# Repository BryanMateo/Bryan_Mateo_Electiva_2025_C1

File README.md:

# Bryan_Mateo_Electiva_2025_C1
Repositorio de la asignatura Electiva Mecatrónica 2025-C1.

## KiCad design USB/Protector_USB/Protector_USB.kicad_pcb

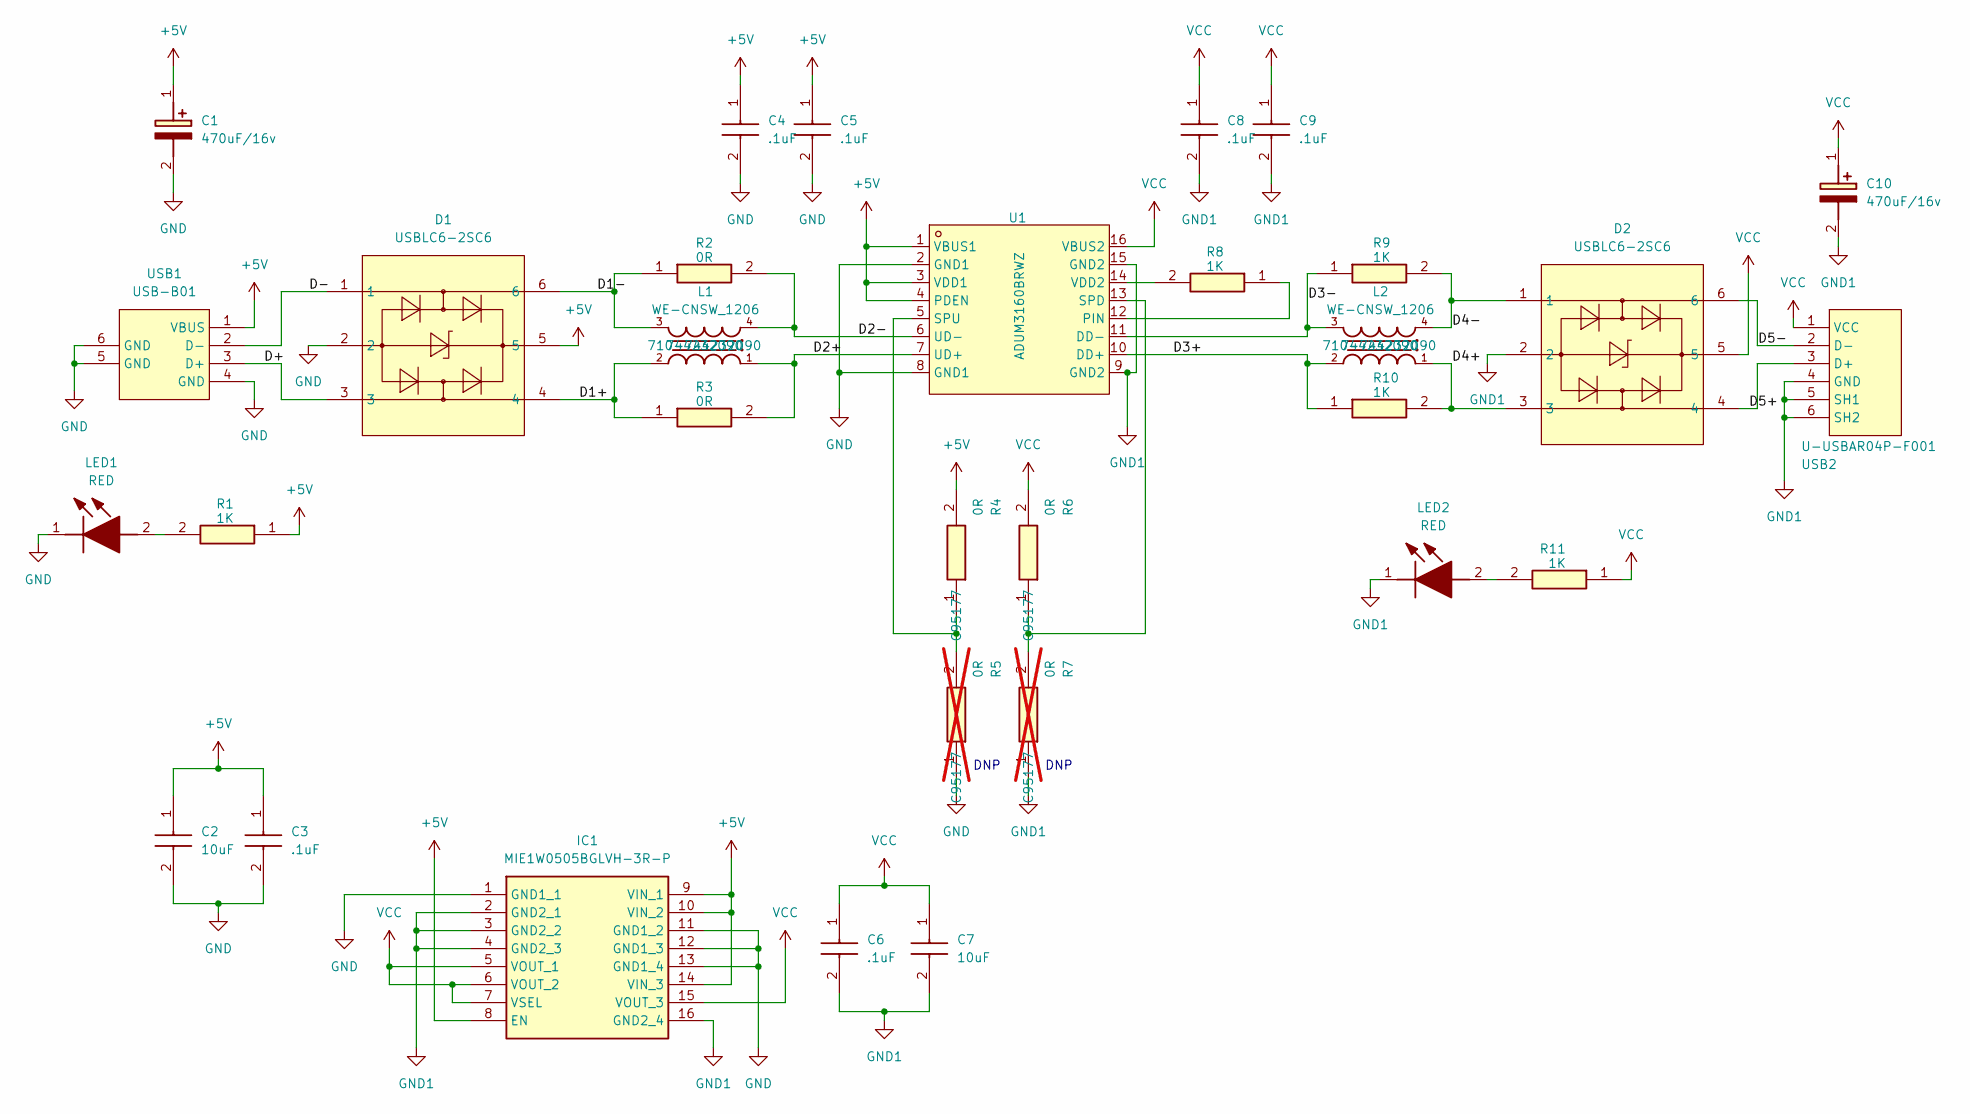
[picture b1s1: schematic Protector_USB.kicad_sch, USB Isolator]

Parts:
C1, C10: 470uF/16v; EEE1AA220WR; Mouser Part Number 667-EEE-FN1C470UR
C2, C7: 10uF; CAPC1608X102N; Mouser Part Number 581-0603YD106KAT2A
C3, C4, C5, C6, C8, C9: .1uF; CAPC1608X90N; Mouser Part Number 581-0603YC104J4T2A
D1, D2: USBLC6-2SC6; SOT-23-6_L2.9-W1.6-P0.95-LS2.8-BL; LCSC Part C7519
IC1: MIE1W0505BGLVH-3R-P; MIE1W0505BGLVH3RP; Mouser Part Number 946-MIE1W0505BGLVH3P
L1, L2: WE-CNSW_1206; WE-CNSW_1206_WE-CNSW_1206; Manufacturer_Part_Number 744232090; Mouser Part Number 710-744232090
LED1, LED2: RED; KSEELP4122P1R258A8J8020R18; Mouser Part Number 720-P412P1R258A8J802
R1, R8, R9, R10, R11: 1K; RESC1608X55N; Mouser Part Number 603-RT0603FRE071KL
R2, R3: 0R; RESC1608X55N; Mouser Part Number 603-RC0603FR-070RL; LCSC Part C95177
R4, R6: 0R; RESC1608X55N; Mouser Part Number 603-RC0603FR-070RL
R5, R7: 0R; RESC1608X55N; Mouser Part Number 603-RC0603FR-070RL; not fitted
U1: ADUM3160BRWZ; WSOIC-16_L10.3-W7.5-P1.27-LS10.3-BL; LCSC Part C108501
USB1: USB-B01; USB-B-TH_USB-B01; LCSC Part C498173
USB2: U-USBAR04P-F001; USB-A-TH_USB-302-T; LCSC Part C386736

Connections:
+5V: C1.1 (+), C2.1, C3.1, C4.1, C5.1, D1.5, IC1.8 (EN), IC1.9 (VIN_1), IC1.10 (VIN_2), IC1.14 (VIN_3), R1.1, R4.2, U1.1 (VBUS1), U1.3 (VDD1), U1.4 (PDEN), USB1.1 (VBUS)
/D1+: D1.4, L1.2, R3.1
/D1-: D1.6, L1.3, R2.1
/D2+: L1.1, R3.2, U1.7 (UD+)
/D2-: L1.4, R2.2, U1.6 (UD-)
/D3+: L2.2, R10.1, U1.10 (DD+)
/D3-: L2.3, R9.1, U1.11 (DD-)
/D4+: D2.3, L2.1, R10.2
/D4-: D2.1, L2.4, R9.2
/D5+: D2.4, USB2.3 (D+)
/D5-: D2.6, USB2.2 (D-)
/D+: D1.3, USB1.3 (D+)
/D-: D1.1, USB1.2 (D-)
GND: C1.2 (-), C2.2, C3.2, C4.2, C5.2, D1.2, IC1.1 (GND1_1), IC1.11 (GND1_2), IC1.12 (GND1_3), IC1.13 (GND1_4), LED1.1 (K), R5.1, U1.2 (GND1), U1.8 (GND1), USB1.4 (GND), USB1.5 (GND), USB1.6 (GND)
GND1: C6.2, C7.2, C8.2, C9.2, C10.2 (-), D2.2, IC1.2 (GND2_1), IC1.3 (GND2_2), IC1.4 (GND2_3), IC1.16 (GND2_4), LED2.1 (K), R7.1, U1.9 (GND2), U1.15 (GND2), USB2.4 (GND), USB2.5 (SH1), USB2.6 (SH2)
unnamed: LED1.2 (A), R1.2
unnamed: LED2.2 (A), R11.2
unnamed: R8.1, U1.12 (PIN)
unnamed: R6.1, R7.2, U1.13 (SPD)
unnamed: R4.1, R5.2, U1.5 (SPU)
unnamed: R8.2, U1.14 (VDD2)
VCC: C6.1, C7.1, C8.1, C9.1, C10.1 (+), D2.5, IC1.5 (VOUT_1), IC1.6 (VOUT_2), IC1.7 (VSEL), IC1.15 (VOUT_3), R6.2, R11.1, U1.16 (VBUS2), USB2.1 (VCC)

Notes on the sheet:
DNP

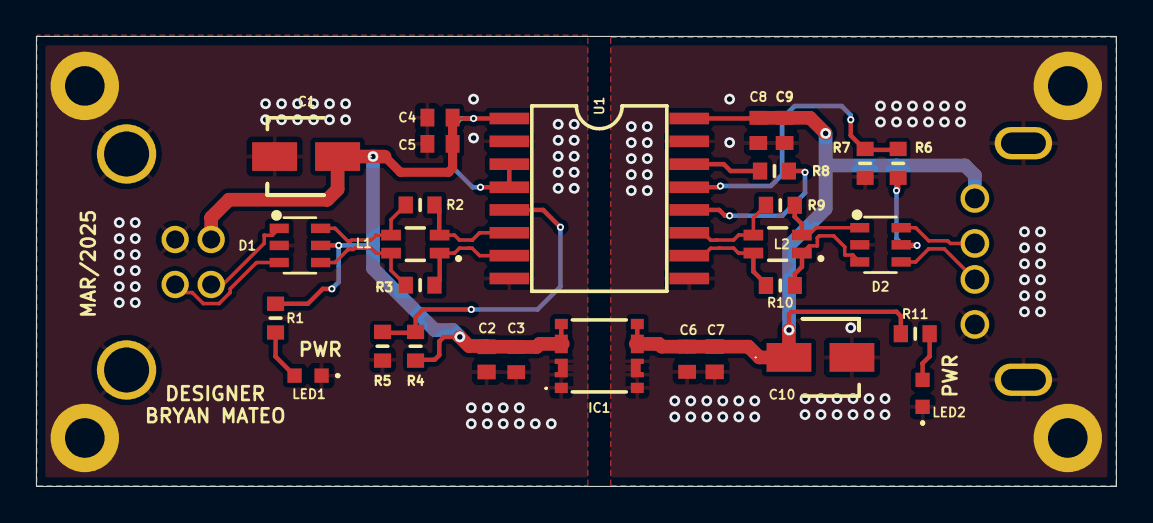
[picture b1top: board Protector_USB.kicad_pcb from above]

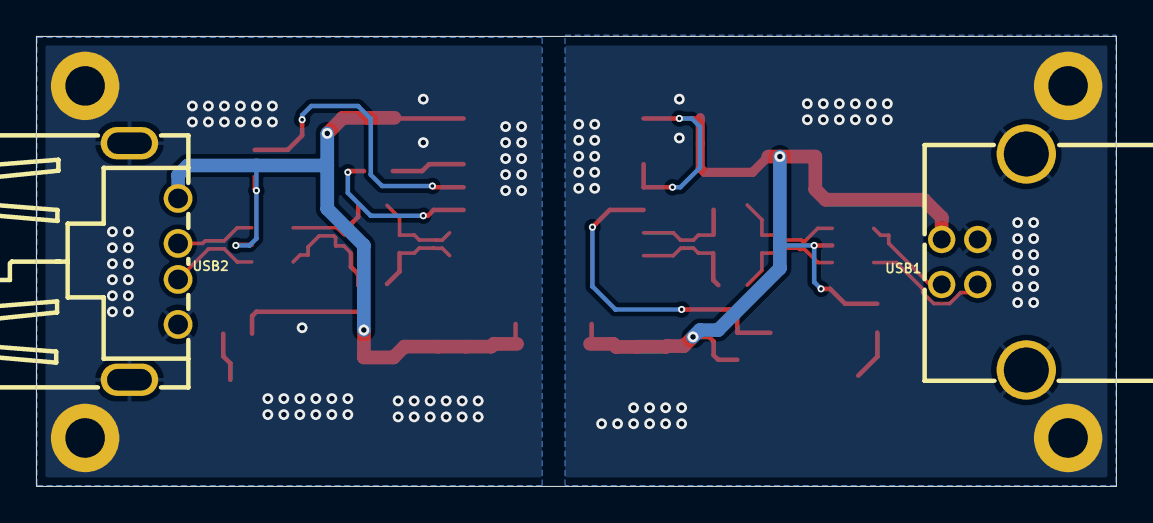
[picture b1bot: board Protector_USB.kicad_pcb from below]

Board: 2 copper layers, 60.0 x 25.0 mm, 31 parts (2 on the bottom side), 22 nets.

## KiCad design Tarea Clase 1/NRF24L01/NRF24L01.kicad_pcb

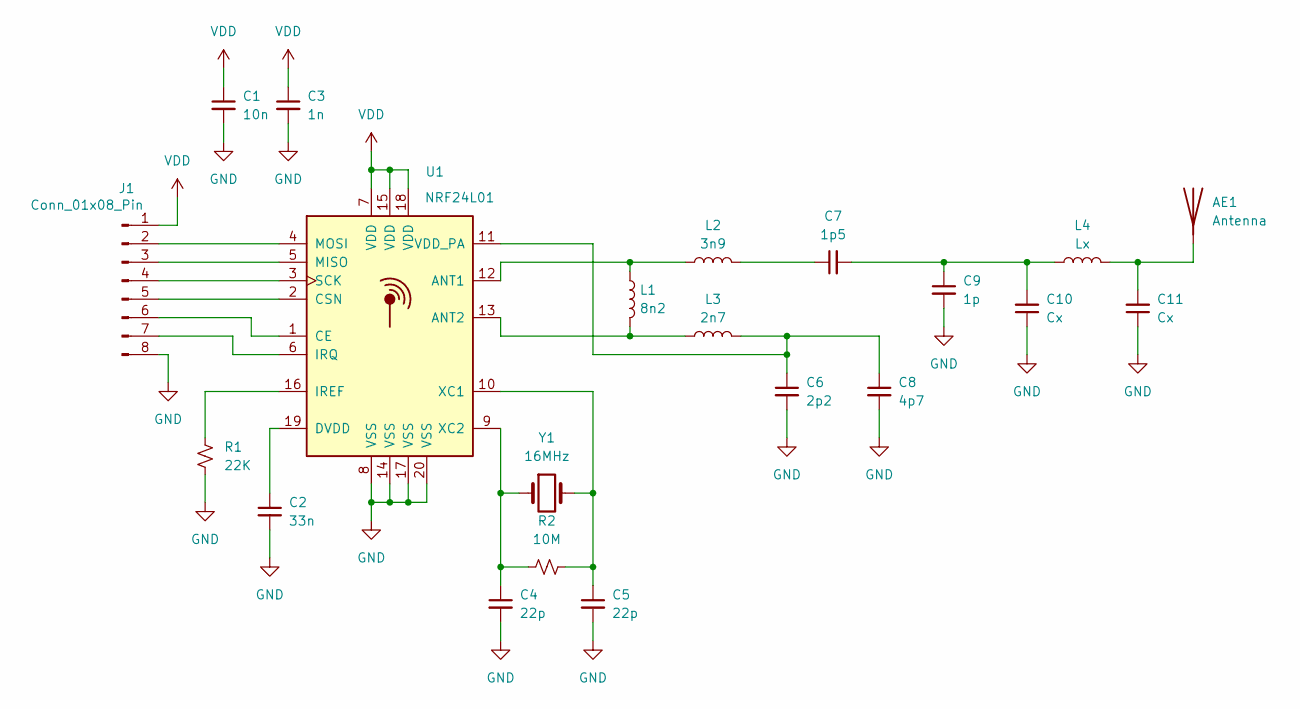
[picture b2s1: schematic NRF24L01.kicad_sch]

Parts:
AE1: Antenna; Texas_SWRA117D_2.4GHz_Right
C1: 10n; C_0402_1005Metric
C2: 33n; C_0402_1005Metric
C3: 1n; C_0402_1005Metric
C4, C5: 22p; C_0402_1005Metric
C6: 2p2; C_0402_1005Metric
C7: 1p5; C_0402_1005Metric
C8: 4p7; C_0402_1005Metric
C9: 1p; C_0402_1005Metric
C10, C11: Cx; C_0402_1005Metric
J1: Conn_01x08_Pin; Hirose_DF13-08P-1.25DSA_1x08_P1.25mm_Vertical
L1: 8n2; L_0402_1005Metric
L2: 3n9; L_0402_1005Metric
L3: 2n7; L_0402_1005Metric
L4: Lx; L_0402_1005Metric
R1: 22K; C_0402_1005Metric
R2: 10M; C_0402_1005Metric
U1: NRF24L01; QFN-20-1EP_4x4mm_P0.5mm_EP2.5x2.5mm
Y1: 16MHz; Crystal_SMD_3215-2Pin_3.2x1.5mm

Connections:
GND: AE1.2, C1.2, C2.2, C3.2, C4.2, C5.2, C6.2, C8.2, C9.2, C10.1, C11.1, J1.8, R1.2, U1.8 (VSS), U1.14 (VSS), U1.17 (VSS), U1.20 (VSS)
unnamed: AE1.1 (A), C11.2, L4.2
unnamed: C7.1, L2.2
unnamed: C7.2, C9.1, C10.2, L4.1
unnamed: J1.2, U1.4 (MOSI)
unnamed: J1.3, U1.5 (MISO)
unnamed: J1.4, U1.3 (SCK)
unnamed: J1.5, U1.2 (CSN)
unnamed: J1.6, U1.1 (CE)
unnamed: J1.7, U1.6 (IRQ)
unnamed: L1.1, L2.1, U1.12 (ANT1)
unnamed: L1.2, L3.1, U1.13 (ANT2)
unnamed: C2.1, U1.19 (DVDD)
unnamed: R1.1, U1.16 (IREF)
unnamed: C6.1, C8.1, L3.2, U1.11 (VDD_PA)
unnamed: C5.1, R2.2, U1.10 (XC1), Y1.2
unnamed: C4.1, R2.1, U1.9 (XC2), Y1.1
VDD: C1.1, C3.1, J1.1, U1.7 (VDD), U1.15 (VDD), U1.18 (VDD)

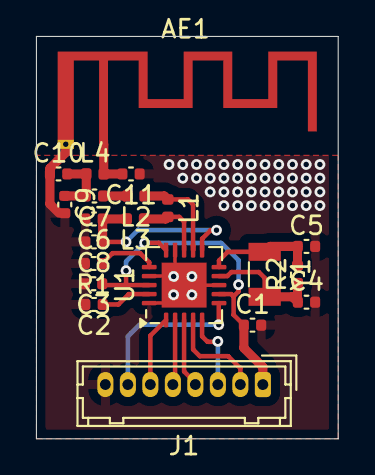
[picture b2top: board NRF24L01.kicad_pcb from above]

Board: 2 copper layers, 16.8 x 22.4 mm, 21 parts (0 on the bottom side), 18 nets.

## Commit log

2025-01-22 Circuito NRF24L01 listo
    Board del video listo
2025-01-24 Resumen
    Resumen libro Matematicas para la computacion
    -Capitulo 1 y 2
2025-03-14 Circuito Aislador USB
2025-04-24 Tapa un 75%
2025-04-24 Tapa 75%*
2025-04-24 Modelo en FreeCad terminado
2025-04-25 Tarea Final
2025-04-26 Medidas de la caja Tarea Final
